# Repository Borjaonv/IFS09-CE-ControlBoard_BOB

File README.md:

# IFS09-ES_ControlBoard_BOB

Hardware design, KiCad schematics and PCB layout for the IFS09 Control board (ISC Formula Student 2026/27).

---

## Getting started

1. Create a GitHub account if you don't have one yet.
2. Download and install [GitHub Desktop](https://desktop.github.com/) (beginner) or [Git CLI](https://git-scm.com/book/en/v2/Getting-Started-Installing-Git) (advanced).

   - If this is your first time using GitHub Desktop, make sure to read the [User Manual](https://help.github.com/desktop/guides/).
   - If this is your first time using Git, start with a tutorial. There are many available online:
     - [Git Tutorial](https://git-scm.com/docs/gittutorial)
     - [Atlassian Git Tutorial](https://www.atlassian.com/git/tutorials/)
   - Keep a copy of [GitHub's Git Cheat Sheet](https://services.github.com/kit/downloads/github-git-cheat-sheet.pdf) handy as a reference.

3. Clone this repository to your machine (update these links!!):
   - SSH: `git@github.com:isc-fs/IFS09-ES_ControlBoard_BOB.git`
   - HTTPS: `https://github.com/isc-fs/IFS09-ES_ControlBoard_BOB.git`

---

## How we work with this repository

### Main branches

The repository has two permanent branches:

**`main`** is the production branch. It contains only validated code that can be flashed onto the car. Never work directly on it.

**`dev`** is the development branch. It is the integration point where everyone's work comes together. Never work directly on it either — all changes arrive through a feature branch.

```
main  ──────────────────●──────────────────────●──▶  (validated releases only)
                        ↑                      ↑
dev   ──────●───●───●───●───●───●───●───●───●──●──▶  (continuous integration)
            ↑   ↑       ↑   ↑   ↑       ↑   ↑
          feat/1 fix/1 feat/2 fix/2   feat/3 fix/3
```

### Feature branches

All work — whether a new feature or a bug fix — is done on a **feature branch** created from `dev`. When the work is ready, a Pull Request is opened toward `dev`, reviewed, merged, and the branch is deleted.

There are two branch types, each with its own independent numeric counter:

```
feat/<n>   →  new functionality  (feat/1, feat/2, feat/3 ...)
fix/<n>    →  bug fix            (fix/1,  fix/2,  fix/3  ...)
```

The `feat` and `fix` counters are independent: `feat/2` and `fix/2` can exist at the same time with no conflict.

### Tracking branch history

Feature branches are deleted after merging to keep the repository clean. The history of each branch is preserved in **GitHub Issues**.

Every branch has one associated issue. The issue carries a **label** (`feat` or `fix`) and its title includes the branch number, for example: `[feat/3] Add CAN broadcast for mission state`. When the branch is merged and deleted, the issue is closed — becoming a permanent record of all the work done.

To see which branches are currently active: filter issues by label and status `open`.
To browse the full history: filter by label and status `closed`.
The number for the next branch of each type is the last closed issue of that type plus one.

> Example: if the last closed issue with label `feat` is `[feat/4] ...`, the next feature branch will be `feat/5`.

---

## Automation

The repository includes a GitHub Actions workflow that manages tracking issues automatically. No setup is required — it works for every developer as soon as they create a branch.

### Automatic issue creation

When a `feat/*` or `fix/*` branch is pushed to GitHub, the workflow automatically opens an issue with:

- The corresponding `[feat/N]` or `[fix/N]` title
- The correct label (`feat` or `fix`)
- A template with sections for describing the work and adding notes
- The name of the developer who created the branch

### Wrong number warning

If the branch number is not the next expected one (either too low or too high), the issue will display a warning indicating the correct number and asking the developer to delete and recreate the branch with the right name.

### Auto-fill description from first commit

When the developer makes their first commit and pushes it, the workflow automatically updates the *"What does this branch do?"* section of the issue with that commit message.

- If the developer manually edits the issue before pushing their first commit, the workflow will not overwrite the description.
- The description is only updated once — subsequent commits do not modify the issue.

---

## Step-by-step workflow

### 1. Create the branch

```bash
# Make sure you are on an up-to-date dev
git checkout dev
git pull origin dev

# Create your branch using the next available number for its type
# (last closed issue of that type + 1)
git checkout -b feat/5    # or fix/3, depending on that type's counter
```

> To find the right number: go to **Issues → filter by label `feat` or `fix` → sort by newest** and read the last number.

### 2. Push the branch

```bash
git push origin feat/5
```

The tracking issue will be opened automatically on GitHub within seconds.

### 3. Work and commit

```bash
# Make your changes and commit with a clear, descriptive message
git add .
git commit -m "short description of what this commit does"

# Push the changes
git push origin feat/5
```

The message of your **first commit** will be used to automatically fill in the issue description.

### 4. Open a Pull Request

When the work is ready, open a Pull Request on GitHub from your branch toward `dev`. In the PR description write `Closes #<issue-number>` so the issue closes automatically when the PR is merged.

Before requesting a review, check that:
- The code compiles with no errors or warnings
- You have tested the change on the bench if applicable
- The PR targets `dev`, not `main`

### 5. Review and merge

Another team member will review the PR. Once approved, it is merged into `dev` and the branch is deleted. The issue will be closed as a permanent record.

### 6. Merging into main

When `dev` holds a set of validated changes that are ready for the car, a responsible team member opens a Pull Request from `dev` into `main`. This only happens after full firmware validation (HIL/bench).

---

*ISC Racing Team — IFS09 Electronics*

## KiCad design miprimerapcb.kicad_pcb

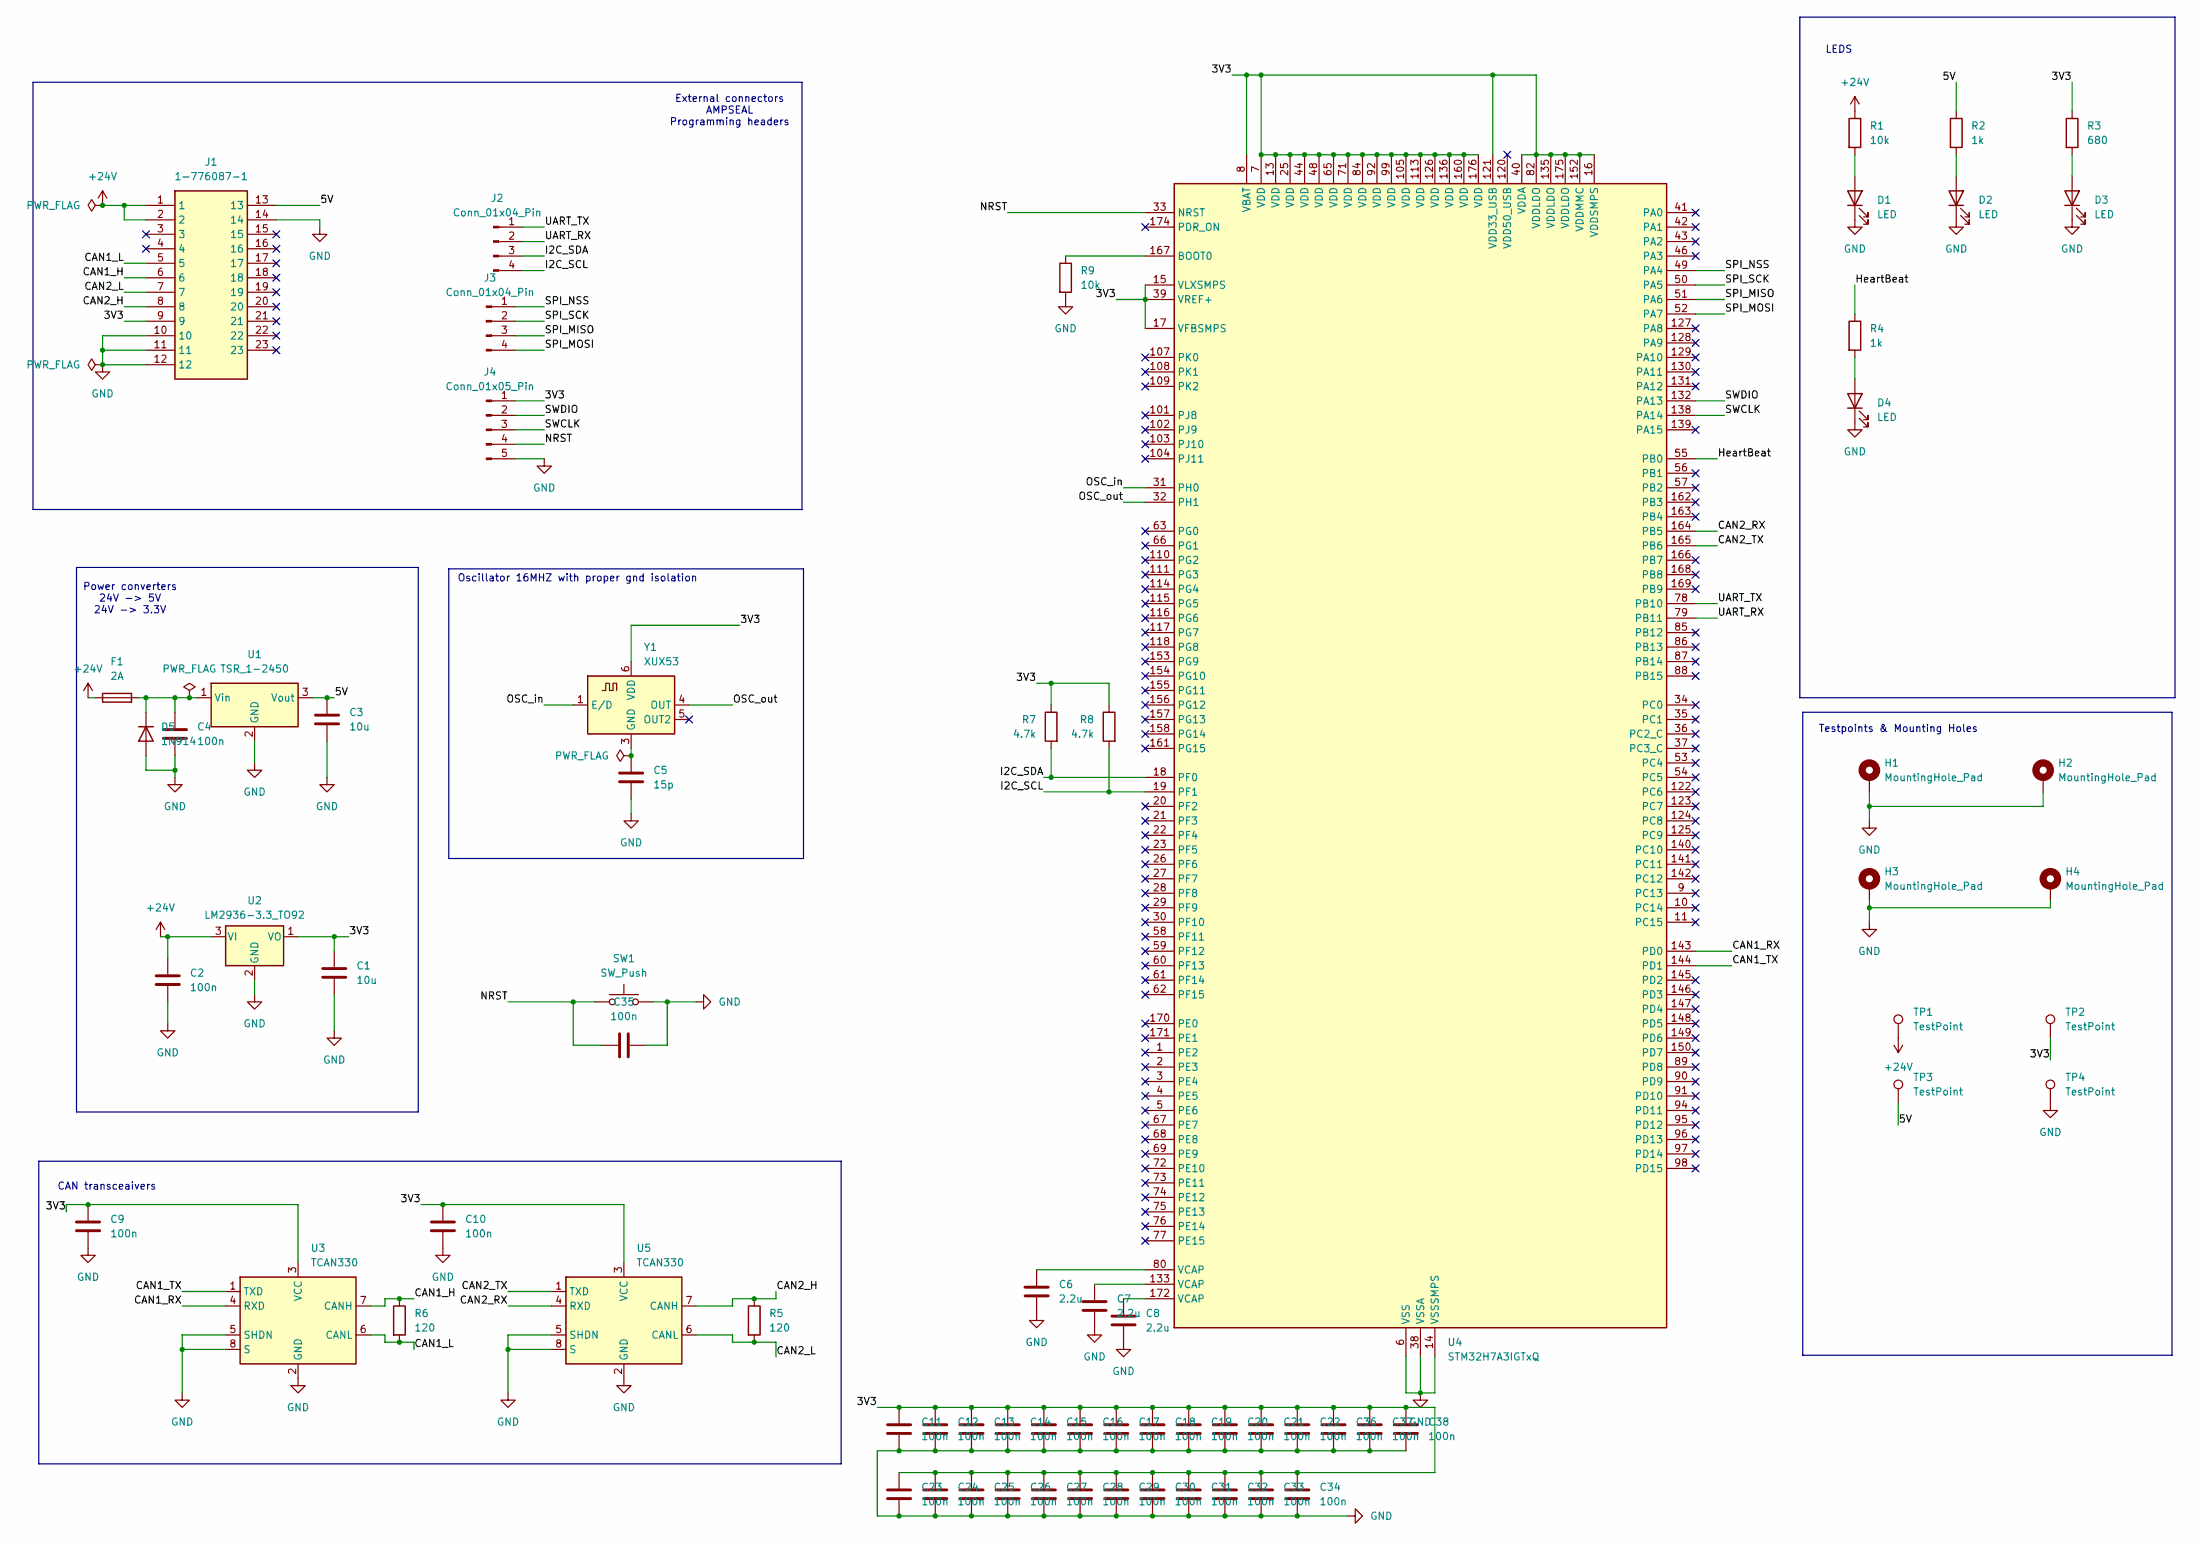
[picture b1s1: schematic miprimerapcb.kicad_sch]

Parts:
C1, C3: 10u; C_0805_2012Metric
C2, C4, C9, C10: 100n; C_0805_2012Metric
C5: 15p; C_0805_2012Metric_Pad1.18x1.45mm_HandSolder
C6, C7, C8: 2.2u; C_0805_2012Metric_Pad1.18x1.45mm_HandSolder
C11, C12, C13, C14, C15, C16, C17, C18, C19, C20, C21, C22, C23, C24, C25, C26, C27, C28, C29, C30, C31, C32, C33, C34, C35, C36, C37, C38: 100n; C_0805_2012Metric_Pad1.18x1.45mm_HandSolder
D1, D2, D3, D4: LED; LED_0805_2012Metric_Pad1.15x1.40mm_HandSolder
D5: 1N914; D_DO-35_SOD27_P7.62mm_Horizontal
F1: 2A; Fuse_0805_2012Metric
H1, H2, H3, H4: MountingHole_Pad; MountingHole_3.2mm_M3_Pad
J1: 1-776087-1; 17760871; Mouser Part Number 571-1-776087-1
J2, J3: Conn_01x04_Pin; PinHeader_1x04_P2.54mm_Vertical
J4: Conn_01x05_Pin; PinHeader_1x06_P2.54mm_Vertical
R1, R9: 10k; R_0805_2012Metric_Pad1.20x1.40mm_HandSolder
R2, R4: 1k; R_0805_2012Metric_Pad1.20x1.40mm_HandSolder
R3: 680; R_0805_2012Metric_Pad1.20x1.40mm_HandSolder
R5, R6: 120; R_0805_2012Metric
R7, R8: 4.7k; R_0805_2012Metric_Pad1.20x1.40mm_HandSolder
SW1: SW_Push; Panasonic_EVQPUK_EVQPUB
TP1, TP2, TP3, TP4: TestPoint; TestPoint_Pad_D2.0mm
U1: TSR_1-2450; Converter_DCDC_TRACO_TSR-1_THT
U2: LM2936-3.3_TO92; TO-92_Inline
U3, U5: TCAN330; SOIC-8_3.9x4.9mm_P1.27mm
U4: STM32H7A3IGTxQ; LQFP-176_24x24mm_P0.5mm
Y1: XUX53; Oscillator_SMD_IDT_JS6-6_5.0x3.2mm_P1.27mm

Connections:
+24V: C2.1, F1.1, J1.1, J1.2, R1.1, TP1.1 (1_1), U2.3 (VI)
/3V3: C1.1, C9.1, C10.1, C11.1, C12.1, C13.1, C14.1, C15.1, C16.1, C17.1, C18.1, C19.1, C20.1, C21.1, C22.1, C23.1, C24.1, C25.1, C26.1, C27.1, C28.1, C29.1, C30.1, C31.1, C32.1, C33.1, C34.1, C36.1, C37.1, C38.1, J1.9, J4.1, R3.1, R7.1, R8.1, TP2.1 (1_1), U2.1 (VO), U3.3 (VCC), U4.7 (VDD), U4.8 (VBAT), U4.13 (VDD), U4.15 (VLXSMPS), U4.16 (VDDSMPS), U4.17 (VFBSMPS), U4.25 (VDD), U4.39 (VREF+), U4.40 (VDDA), U4.44 (VDD), U4.48 (VDD), U4.65 (VDD), U4.71 (VDD), U4.82 (VDDLDO), U4.84 (VDD), U4.92 (VDD), U4.99 (VDD), U4.105 (VDD), U4.113 (VDD), U4.121 (VDD33_USB), U4.126 (VDD), U4.135 (VDDLDO), U4.136 (VDD), U4.152 (VDDMMC), U4.160 (VDD), U4.175 (VDDLDO), U4.176 (VDD), U5.3 (VCC), Y1.6 (VDD)
/5V: C3.1, J1.13, R2.1, TP3.1 (1_1), U1.3 (Vout)
/CAN1_H: J1.6, R6.1, U3.7 (CANH)
/CAN1_L: J1.5, R6.2, U3.6 (CANL)
/CAN1_RX: U3.4 (RXD), U4.143 (PD0)
/CAN1_TX: U3.1 (TXD), U4.144 (PD1)
/CAN2_H: J1.8, R5.1, U5.7 (CANH)
/CAN2_L: J1.7, R5.2, U5.6 (CANL)
/CAN2_RX: U4.164 (PB5), U5.4 (RXD)
/CAN2_TX: U4.165 (PB6), U5.1 (TXD)
/HeartBeat: R4.1, U4.55 (PB0)
/I2C_SCL: J2.4, R8.2, U4.19 (PF1)
/I2C_SDA: J2.3, R7.2, U4.18 (PF0)
/NRST: C35.1, J4.4, SW1.1, U4.33 (NRST)
/OSC_in: U4.31 (PH0), Y1.1 (E/D)
/OSC_out: U4.32 (PH1), Y1.4 (OUT)
/SPI_MISO: J3.3, U4.51 (PA6)
/SPI_MOSI: J3.4, U4.52 (PA7)
/SPI_NSS: J3.1, U4.49 (PA4)
/SPI_SCK: J3.2, U4.50 (PA5)
/SWCLK: J4.3, U4.138 (PA14)
/SWDIO: J4.2, U4.132 (PA13)
/UART_RX: J2.2, U4.79 (PB11)
/UART_TX: J2.1, U4.78 (PB10)
GND: C1.2, C2.2, C3.2, C4.2, C5.2, C6.2, C7.2, C8.2, C9.2, C10.2, C11.2, C12.2, C13.2, C14.2, C15.2, C16.2, C17.2, C18.2, C19.2, C20.2, C21.2, C22.2, C23.2, C24.2, C25.2, C26.2, C27.2, C28.2, C29.2, C30.2, C31.2, C32.2, C33.2, C34.2, C35.2, C36.2, C37.2, C38.2, D1.1 (K), D2.1 (K), D3.1 (K), D4.1 (K), D5.2 (A), H1.1 (1_1), H2.1 (1_1), H3.1 (1_1), H4.1 (1_1), J1.10, J1.11, J1.12, J1.14, J4.5, R9.2, SW1.2, TP4.1 (1_1), U1.2 (GND), U2.2 (GND), U3.2 (GND), U3.5 (SHDN), U3.8 (S), U4.6 (VSS), U4.12 (VSS), U4.14 (VSSSMPS), U4.24 (VSS), U4.38 (VSSA), U4.45 (VSS), U4.47 (VSS), U4.64 (VSS), U4.70 (VSS), U4.81 (VSS), U4.83 (VSS), U4.93 (VSS), U4.100 (VSS), U4.106 (VSS), U4.112 (VSS), U4.119 (VSS), U4.134 (VSS), U4.137 (VSS), U4.151 (VSS), U4.159 (VSS), U4.173 (VSS), U5.2 (GND), U5.5 (SHDN), U5.8 (S)
unnamed: C6.1, U4.80 (VCAP)
unnamed: C7.1, U4.133 (VCAP)
unnamed: C8.1, U4.172 (VCAP)
unnamed: D1.2 (A), R1.2
unnamed: D2.2 (A), R2.2
unnamed: D3.2 (A), R3.2
unnamed: D4.2 (A), R4.2
unnamed: C4.1, D5.1 (K), F1.2, U1.1 (Vin)
unnamed: R9.1, U4.167 (BOOT0)
unnamed: C5.1, Y1.3 (GND)

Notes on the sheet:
Testpoints & Mounting Holes
Power converters 24V -> 5V 24V -> 3.3V
CAN transceaivers
LEDS
External connectors AMPSEAL Programming headers
Oscillator 16MHZ with proper gnd isolation

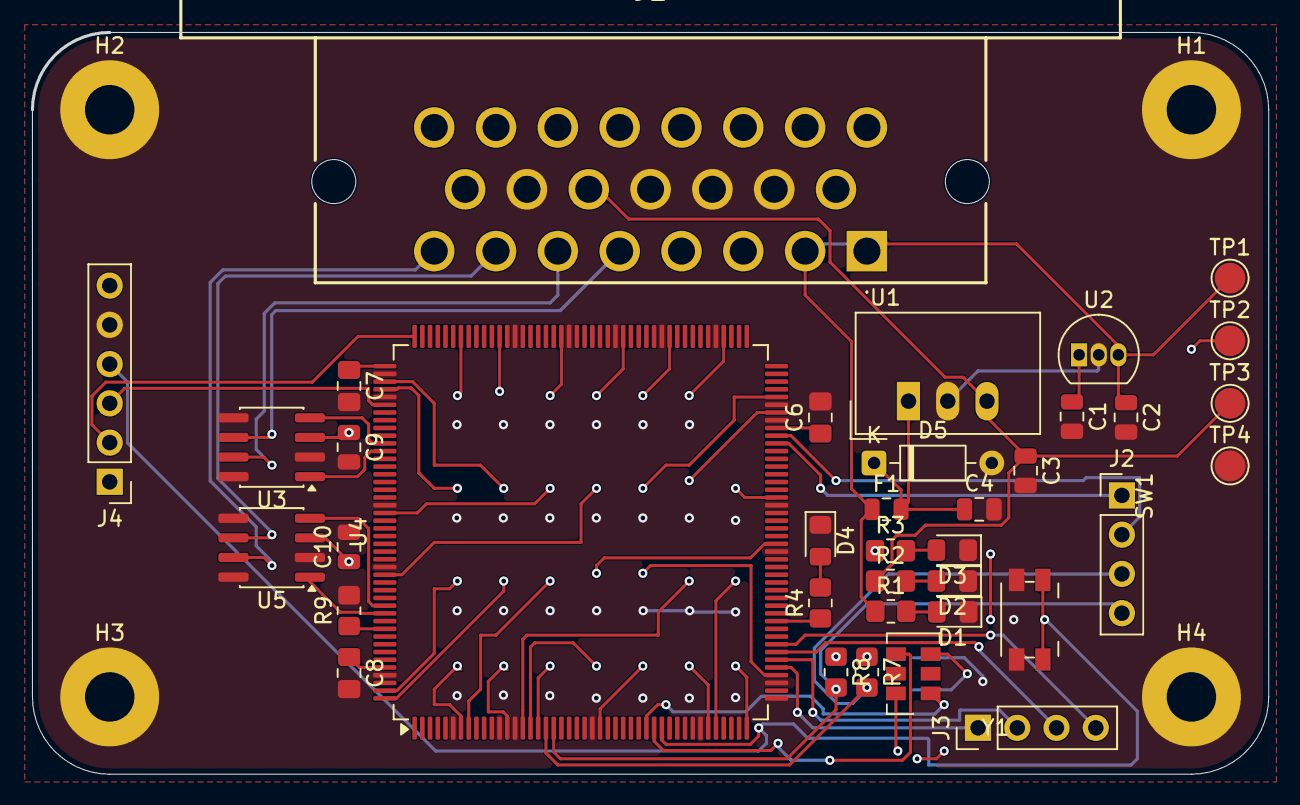
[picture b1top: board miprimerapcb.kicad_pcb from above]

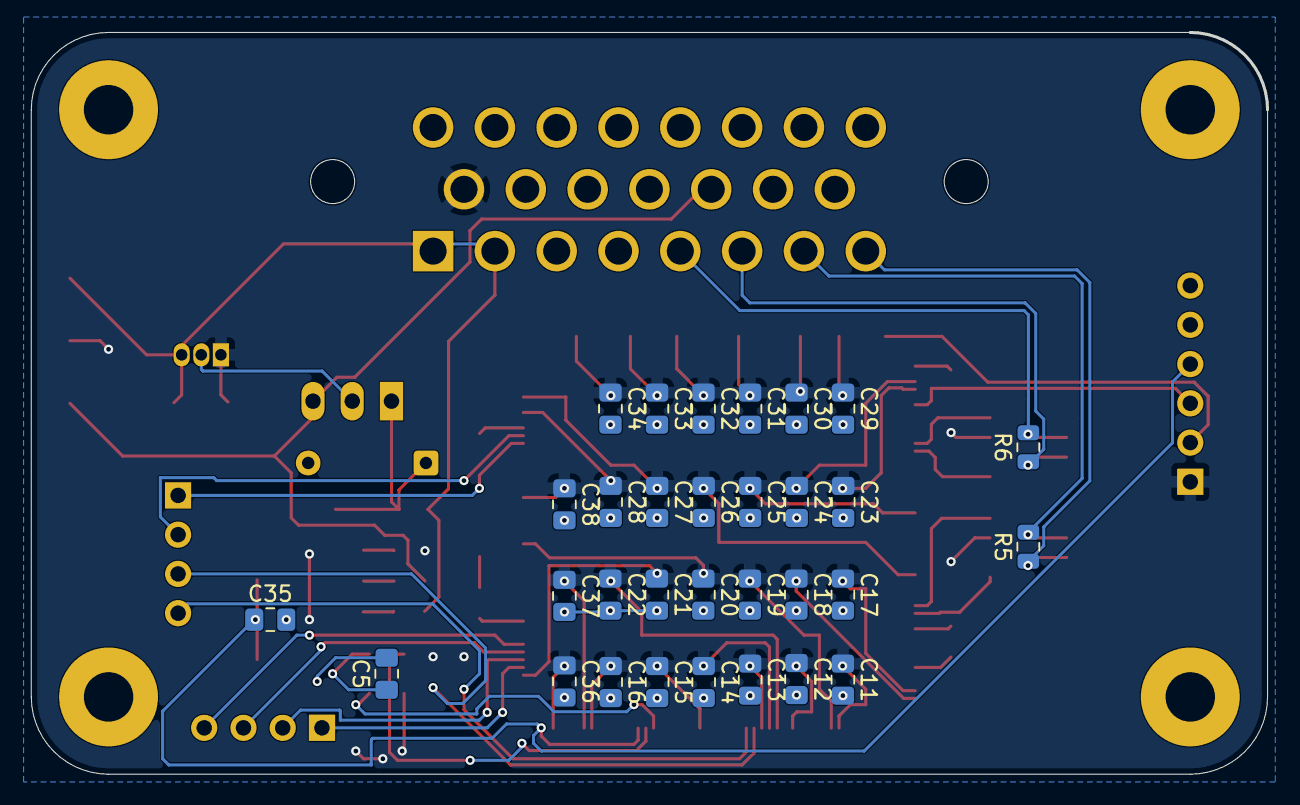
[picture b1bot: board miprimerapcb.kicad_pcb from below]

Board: 2 copper layers, 80.0 x 48.0 mm, 72 parts (31 on the bottom side), 36 nets.
